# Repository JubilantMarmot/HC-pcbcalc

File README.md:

# Button Matrix & Calculator Firmware

This is a button matrix schematic that uses RP2040 to connect to GPIO pins in an efficient manner.

As an example, I also implemented a calculator with [Reverse Polish Notation (RPN)](https://en.wikipedia.org/wiki/Reverse_Polish_notation) using the GPIO pins.

I originally was going to make this into an actual project, but I failed with the schematic as I am not experienced enough.
Nevertheless, this is done really well and the button matrix can be easily copy-pasted into your project..

The code is in the [firmware](./firmware) folder and has a really good example of how to use those GPIO pins in something like a calculator. I added arithmetic operations
and basic functions such as sin cos and tan.

## Images

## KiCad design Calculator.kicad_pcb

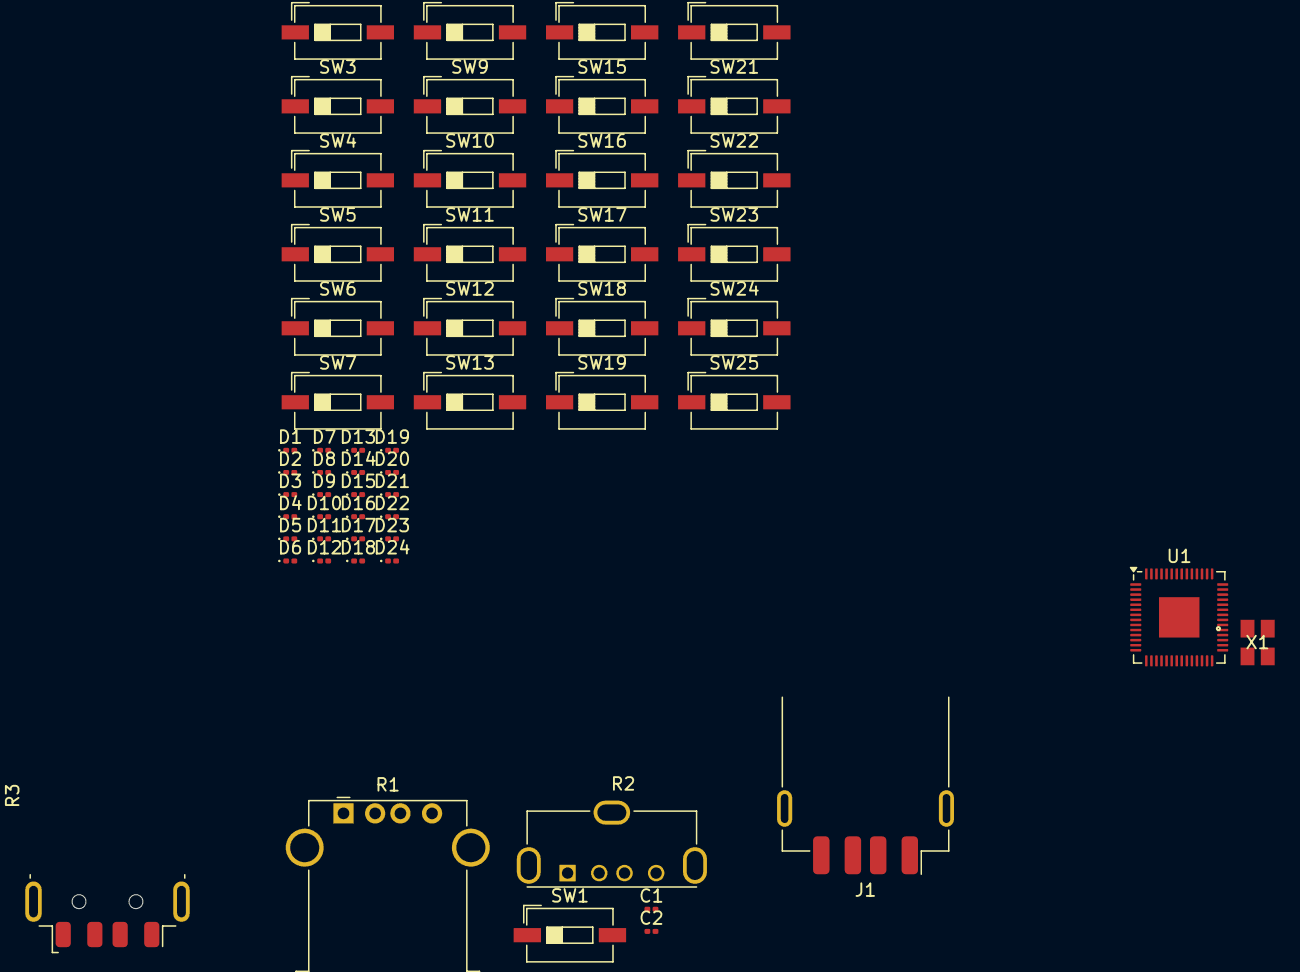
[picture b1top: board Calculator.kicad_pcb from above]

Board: 2 copper layers, 57 parts (0 on the bottom side), 19 nets, no tracks yet.

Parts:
C1, C2: 15pF; C_0201_0603Metric
D1, D2, D3, D4, D5, D6, D7, D8, D9, D10, D11, D12, D13, D14, D15, D16, D17, D18, D19, D20, D21, D22, D23, D24: D; D_0201_0603Metric
J1: USB_A; USB_A_Receptacle_GCT_USB1046
R1: 10k; USB_A_Stewart_SS-52100-001_Horizontal
R2: R; USB_A_Molex_105057_Vertical
R3: 1K; USB_A_Molex_48037-2200_Horizontal
SW1: SW_Push; SW_DIP_SPSTx01_Slide_6.7x4.1mm_W6.73mm_P2.54mm_LowProfile_J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
SW2, SW3, SW4, SW5, SW6, SW7, SW8, SW9, SW10, SW11, SW12, SW13, SW14, SW15, SW16, SW17, SW18, SW19, SW20, SW21, SW22, SW23, SW24, SW25: SW_MEC_5G; SW_DIP_SPSTx01_Slide_6.7x4.1mm_W6.73mm_P2.54mm_LowProfile_J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
U1: RP2040; QFN-56-1EP_7x7mm_P0.4mm_EP3.2x3.2mm
X1: ABM8-272-T3; ABM8-272-T3_ABR

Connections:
BTN_COL1: D1.1 (K), D4.1 (K), D7.1 (K), D10.1 (K), D17.1 (K), D18.1 (K), U1.14 (GPIO11)
BTN_COL2: D2.1 (K), D5.1 (K), D8.1 (K), D11.1 (K), D19.1 (K), D20.1 (K), U1.15 (GPIO12)
BTN_COL3: D3.1 (K), D6.1 (K), D9.1 (K), D12.1 (K), D21.1 (K), D22.1 (K), U1.16 (GPIO13)
BTN_COL4: D13.1 (K), D14.1 (K), D15.1 (K), D16.1 (K), D23.1 (K), D24.1 (K)
BTN_ROW1: SW2.1 (A), SW2.2 (A), SW3.1 (A), SW3.2 (A), SW4.1 (A), SW4.2 (A), SW14.1 (A), SW14.2 (A), U1.9 (GPIO7)
BTN_ROW2: SW5.1 (A), SW5.2 (A), SW6.1 (A), SW6.2 (A), SW7.1 (A), SW7.2 (A), SW15.1 (A), SW15.2 (A), U1.11 (GPIO8)
BTN_ROW3: SW8.1 (A), SW8.2 (A), SW9.1 (A), SW9.2 (A), SW10.1 (A), SW10.2 (A), SW16.1 (A), SW16.2 (A), U1.12 (GPIO9)
BTN_ROW4: SW11.1 (A), SW11.2 (A), SW12.1 (A), SW12.2 (A), SW13.1 (A), SW13.2 (A), SW17.1 (A), SW17.2 (A), U1.13 (GPIO10)
BTN_ROW5: SW18.1 (A), SW18.2 (A), SW20.1 (A), SW20.2 (A), SW22.1 (A), SW22.2 (A), SW24.1 (A), SW24.2 (A)
BTN_ROW6: SW19.1 (A), SW19.2 (A), SW21.1 (A), SW21.2 (A), SW23.1 (A), SW23.2 (A), SW25.1 (A), SW25.2 (A)
GND: C1.1, C2.1, J1.4 (GND), J1.5 (Shield), SW1.1, U1.19 (TESTEN), U1.57 (GND), X1.2, X1.4
unnamed: C2.2, R3.1, X1.3
unnamed: U1.1 (IOVDD), U1.10 (IOVDD), U1.22 (IOVDD), U1.33 (IOVDD), U1.42 (IOVDD), U1.49 (IOVDD)
unnamed: R1.1, SW1.2, U1.26 (RUN)
USB_DN: J1.2 (D-), U1.46 (USB_DM)
USB_DP: J1.3 (D+), U1.47 (USB_DP)
USB_VBUS: J1.1 (VBUS), U1.23 (DVDD), U1.50 (DVDD)
XIN: C1.2, R2.1, U1.20 (XIN), X1.1
XOUT: R2.2, R3.2, U1.21 (XOUT)

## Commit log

2024-08-23 init
2024-08-23 progress
2024-08-25 progres
2024-08-25 rpn implementation
2024-08-25 finalize
